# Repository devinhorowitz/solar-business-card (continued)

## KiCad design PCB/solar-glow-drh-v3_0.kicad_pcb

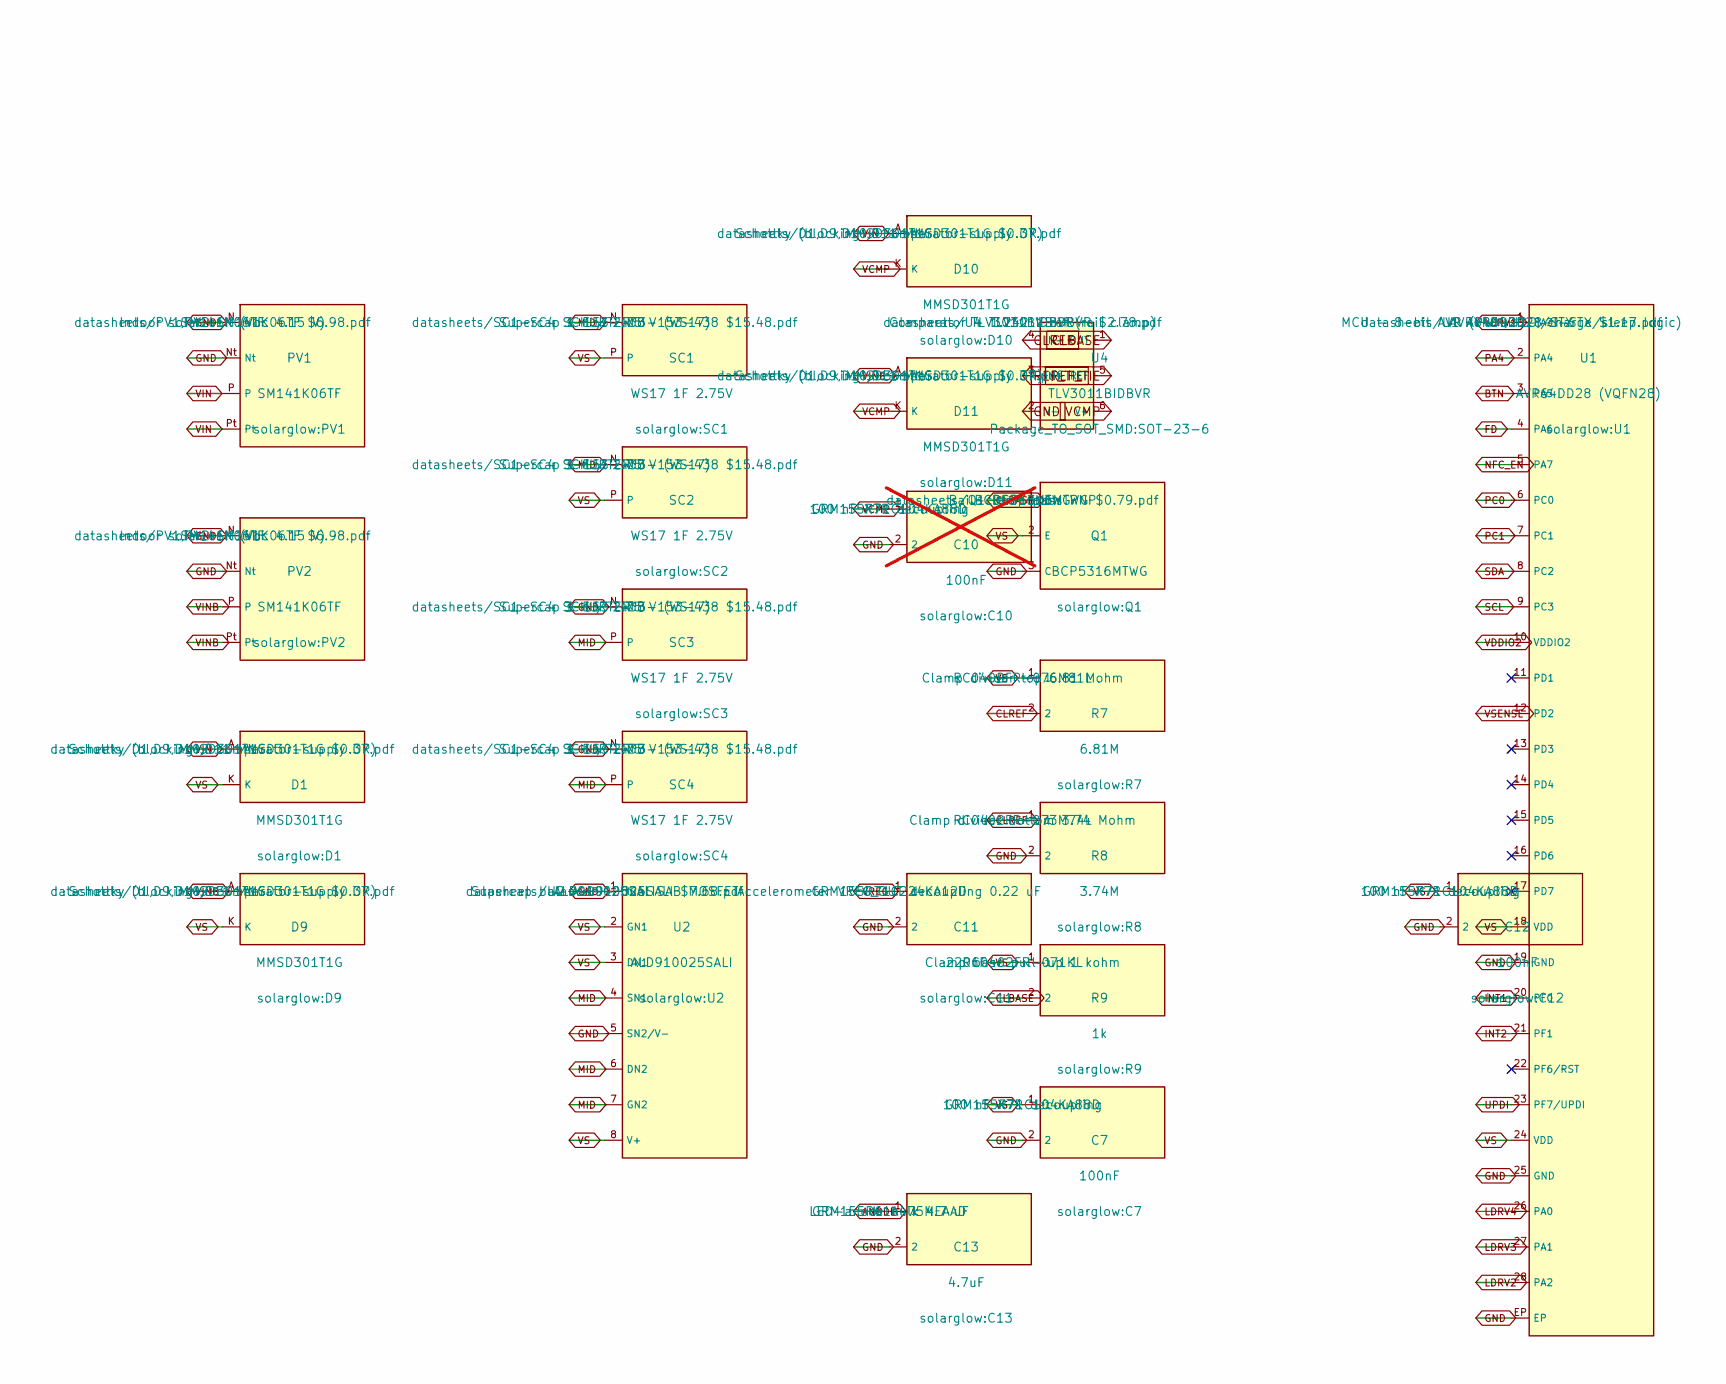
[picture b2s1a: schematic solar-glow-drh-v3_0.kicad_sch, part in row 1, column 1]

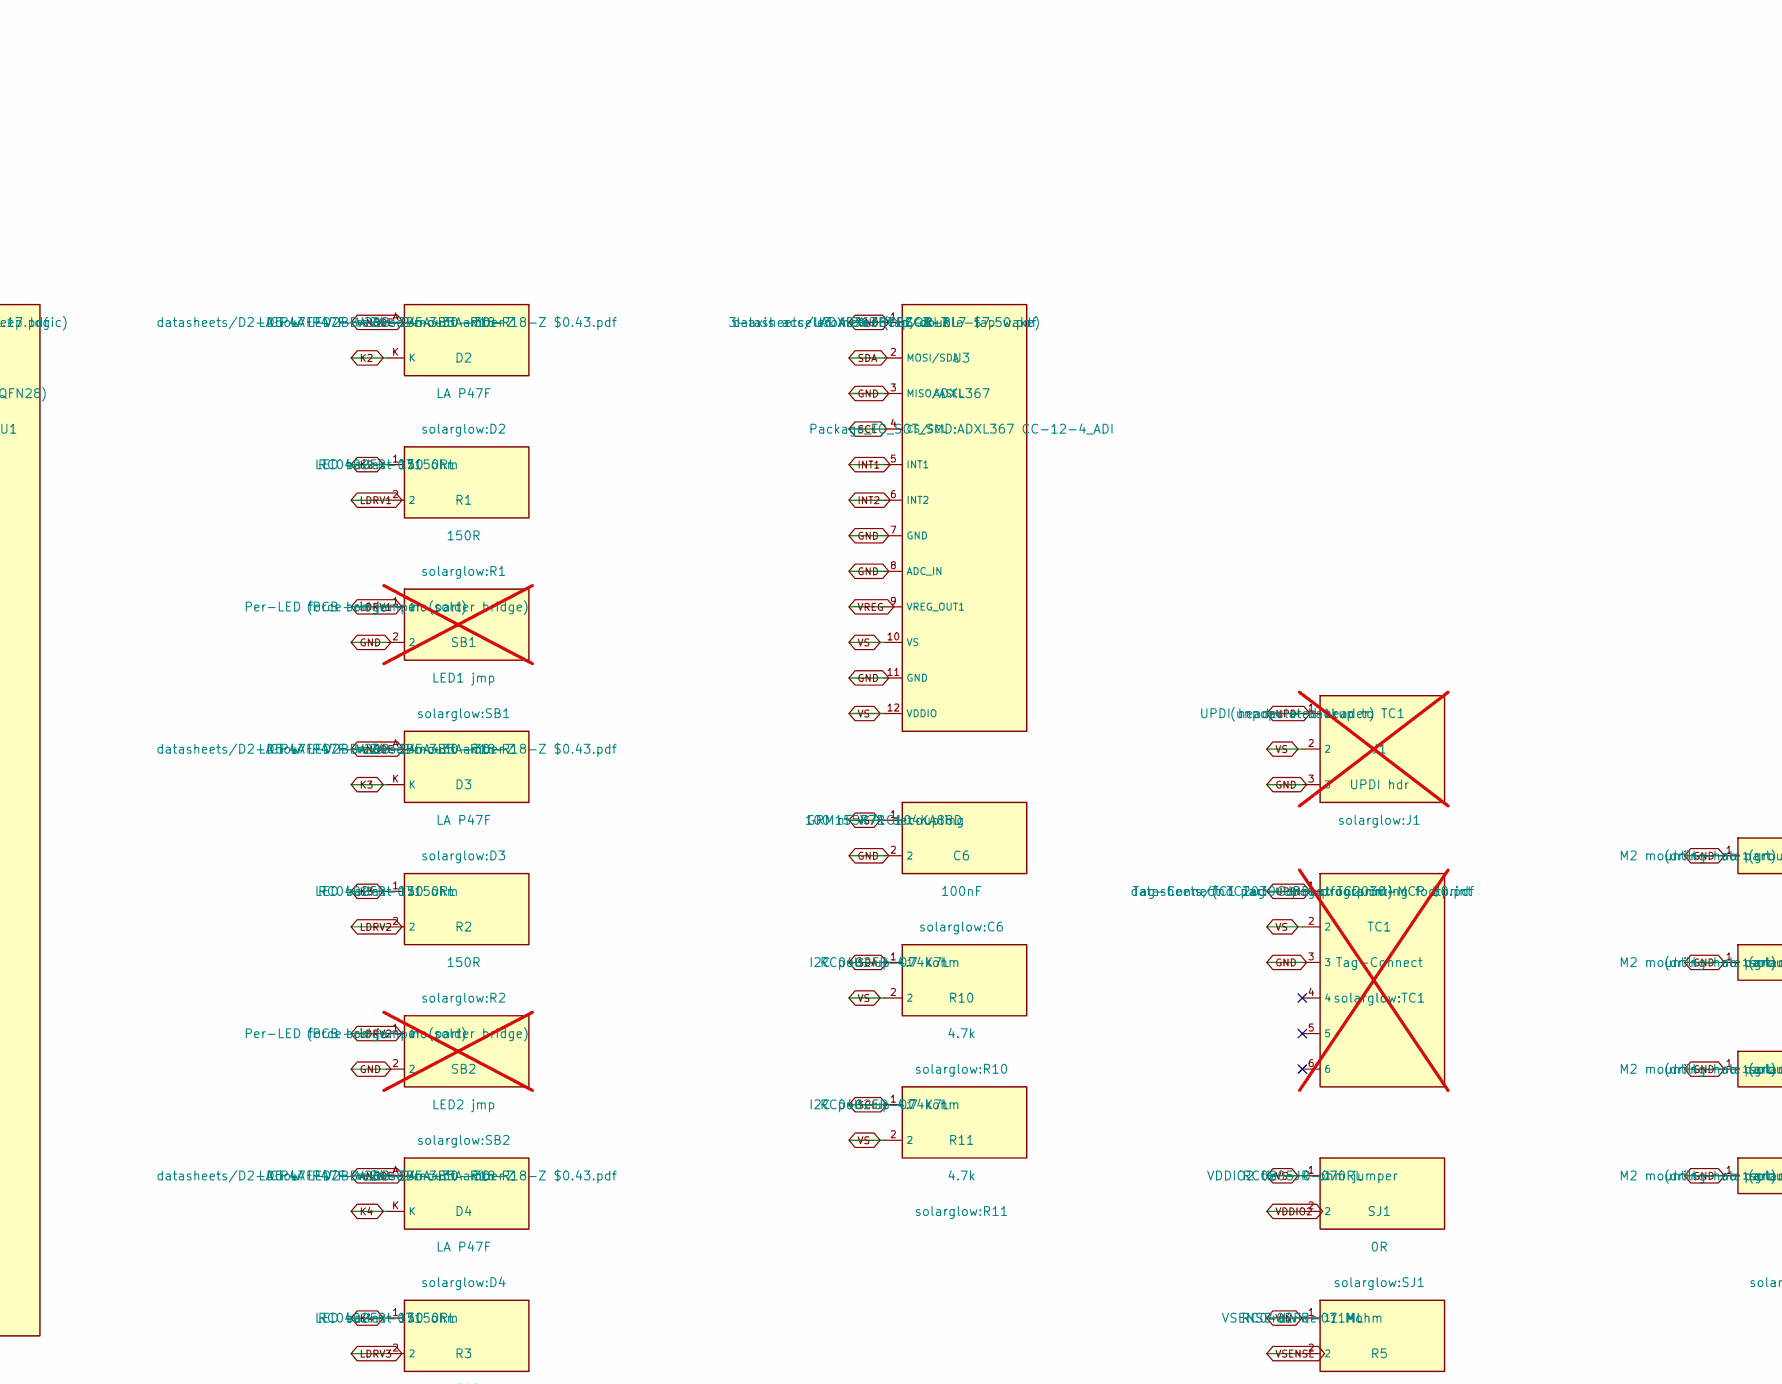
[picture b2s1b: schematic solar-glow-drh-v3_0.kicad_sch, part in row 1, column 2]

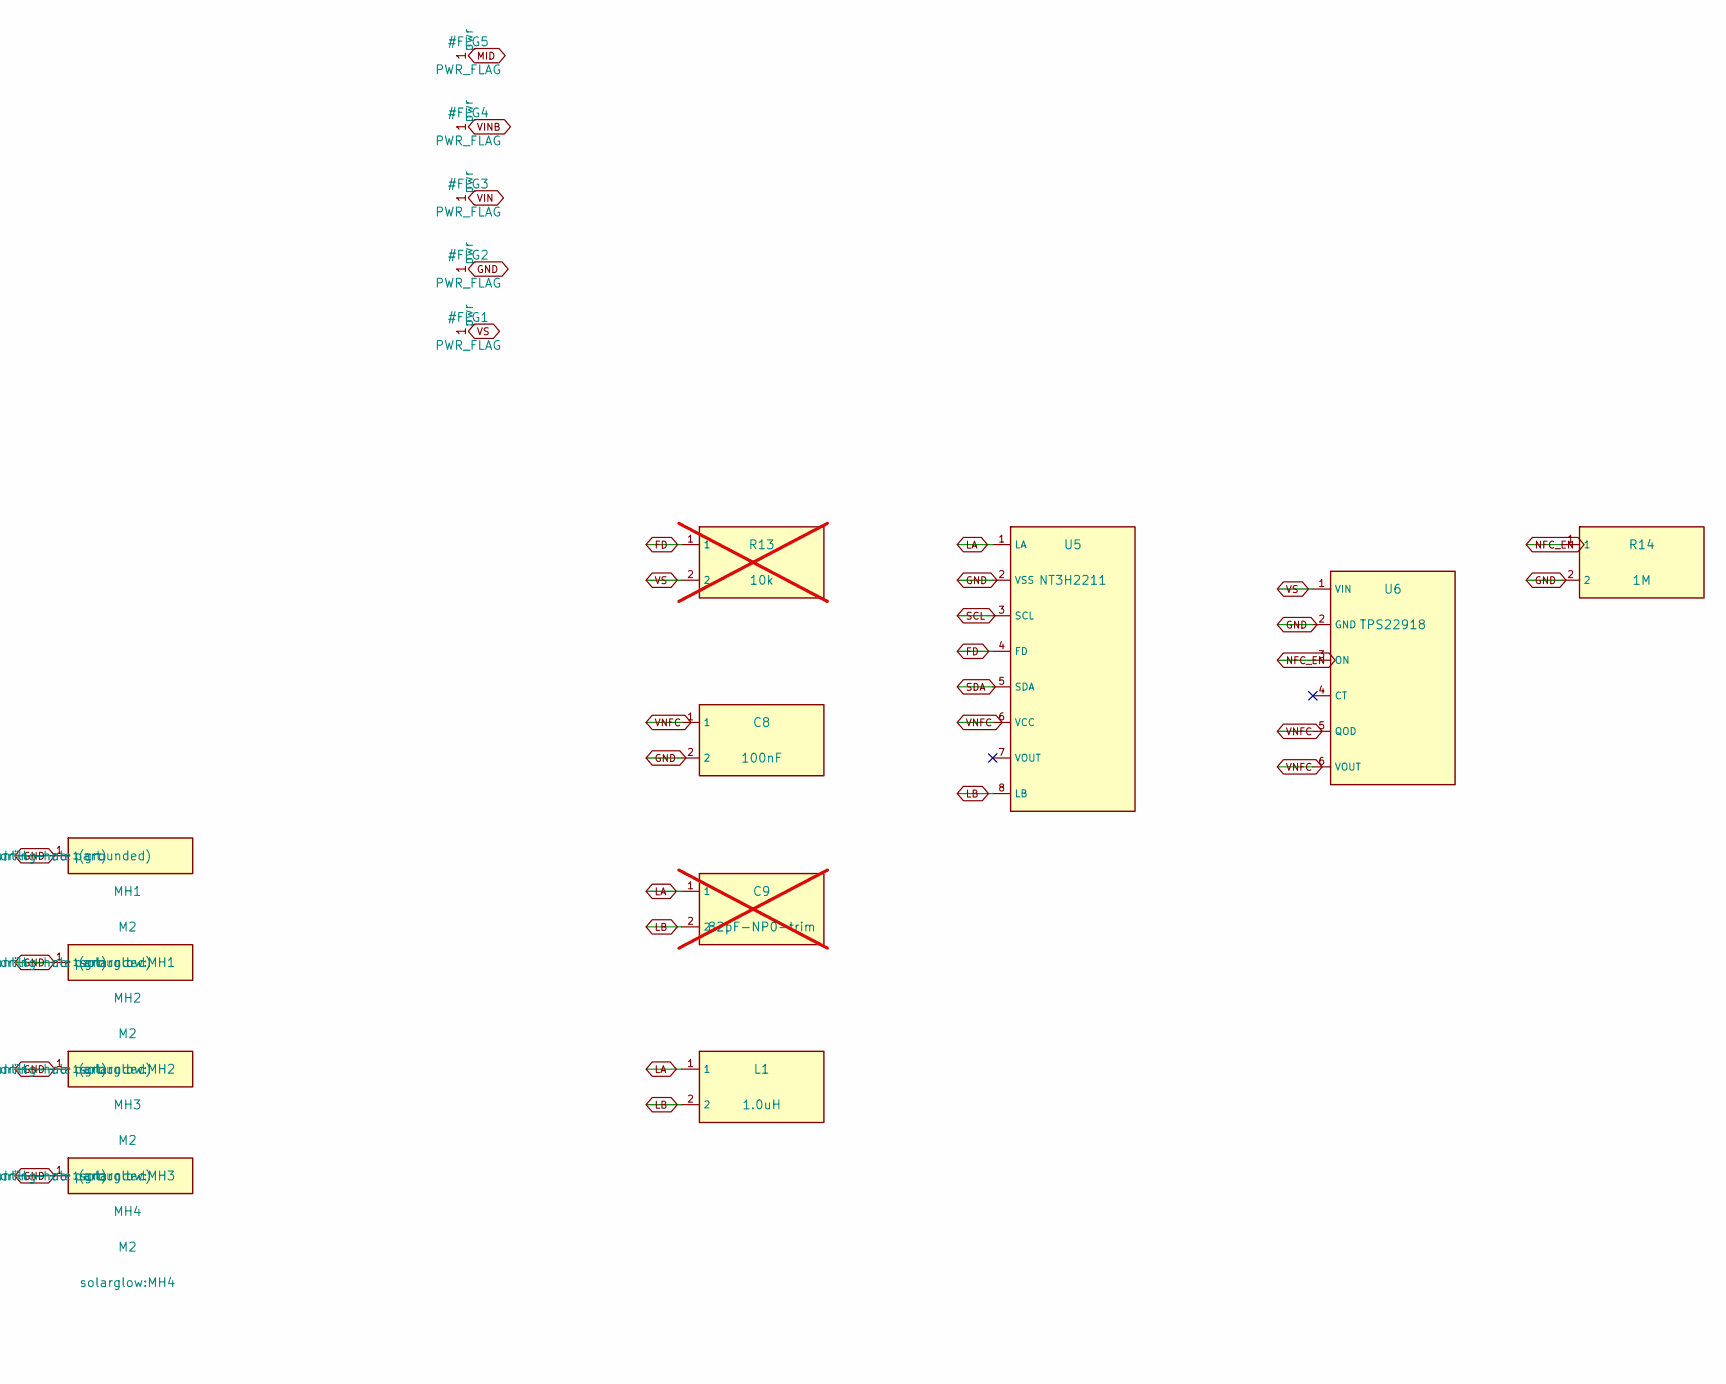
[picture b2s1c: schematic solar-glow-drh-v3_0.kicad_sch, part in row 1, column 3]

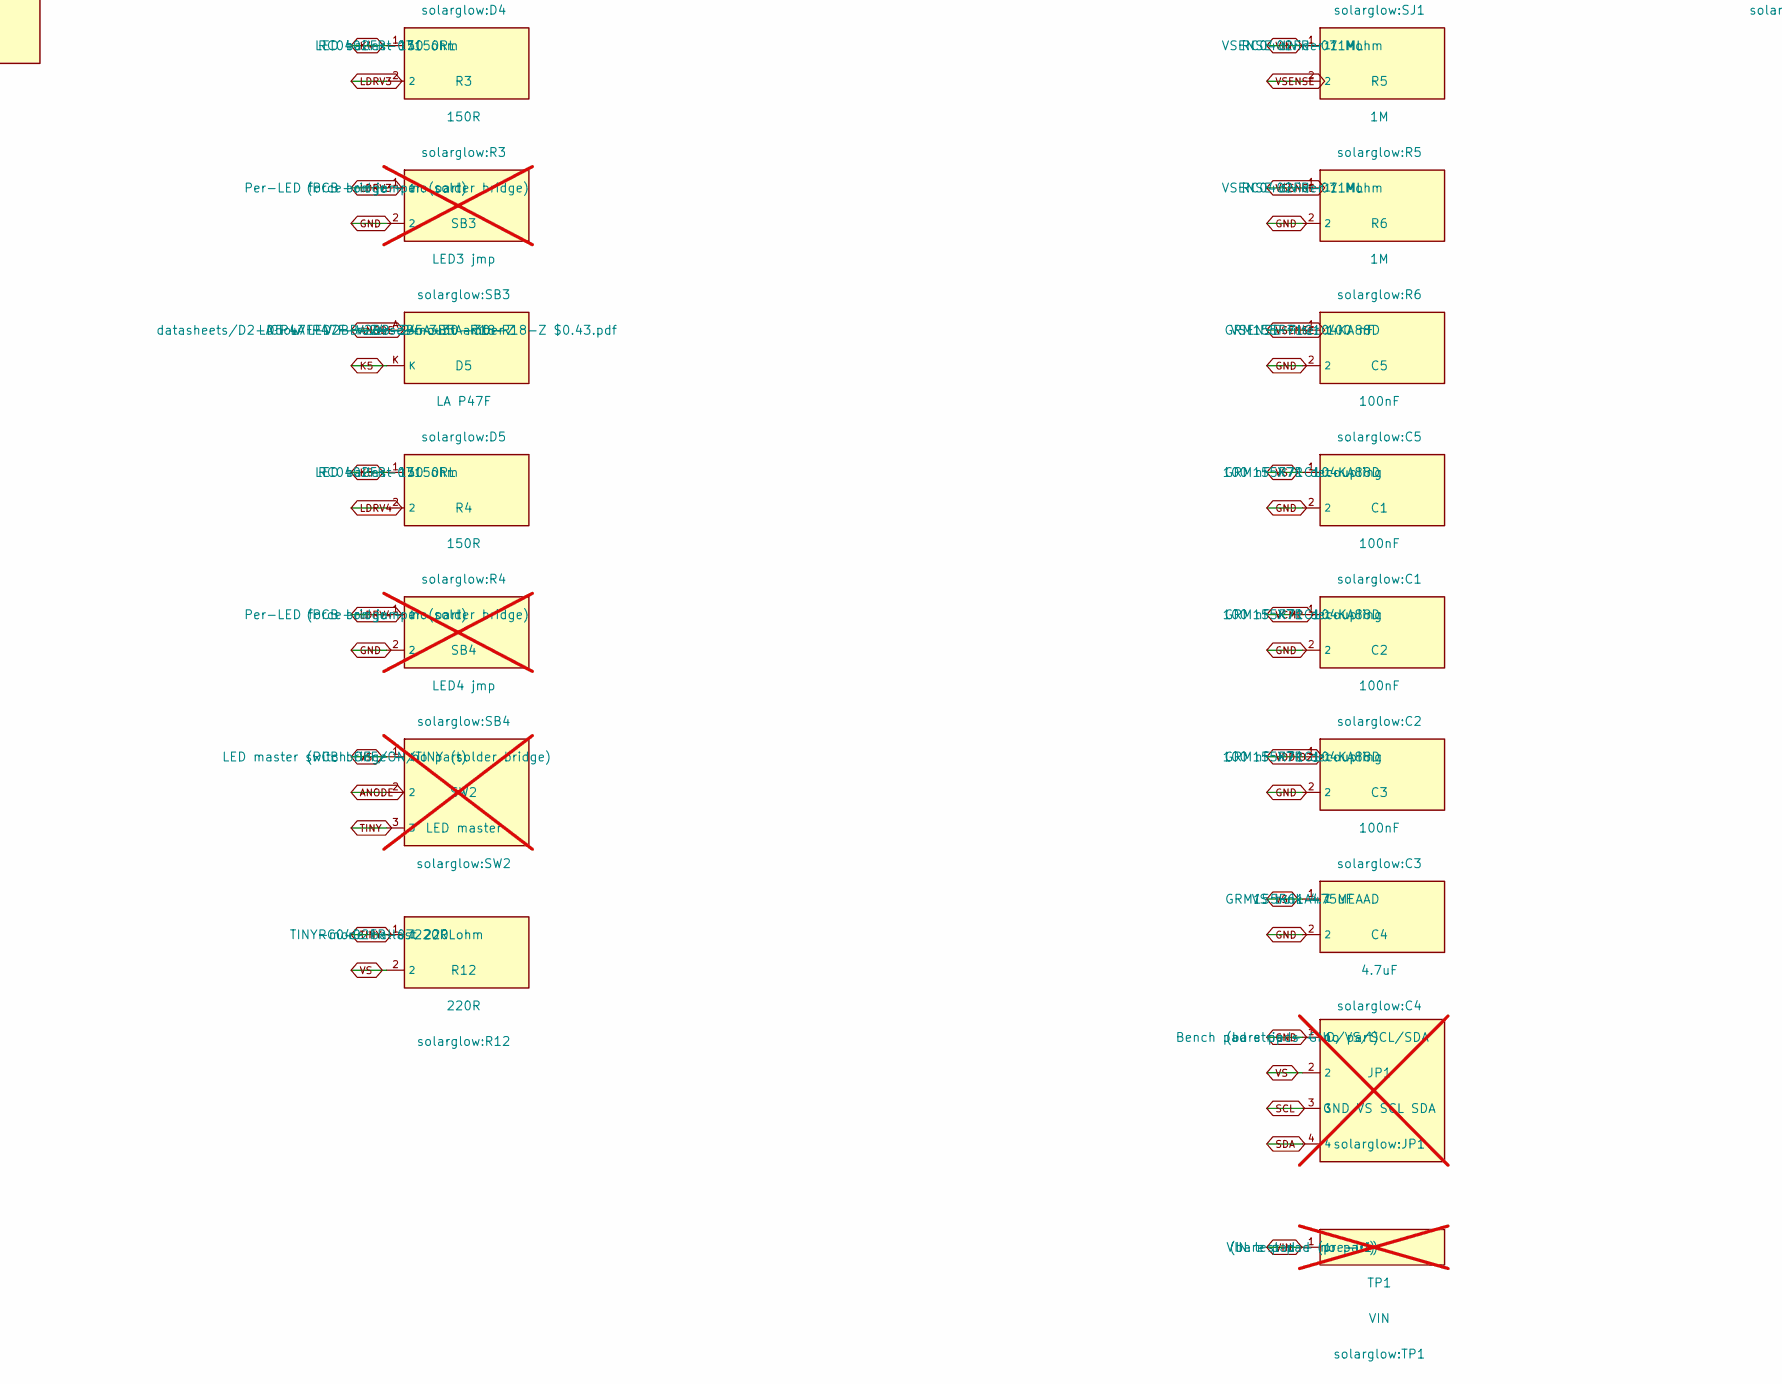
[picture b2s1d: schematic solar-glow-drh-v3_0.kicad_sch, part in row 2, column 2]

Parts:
C1: 100nF; C1; MPN GRM155R71C104KA88D
C2: 100nF; C2; MPN GRM155R71C104KA88D
C3: 100nF; C3; MPN GRM155R71C104KA88D
C4: 4.7uF; C4; MPN GRM155R61A475MEAAD
C5: 100nF; C5; MPN GRM155R71C104KA88D
C6: 100nF; C6; MPN GRM155R71C104KA88D
C7: 100nF; C7; MPN GRM155R71C104KA88D
C8: 100nF; C8; MPN GRM155R71C104KA88D
C9: 82pF-NP0-trim; C9; MPN (DNP); not fitted
C10: 100nF; C10; MPN GRM155R71C104KA88D; not fitted
C11: 220nF; C11; MPN GRM155R71C224KA12D
C12: 100nF; C12; MPN GRM155R71C104KA88D
C13: 4.7uF; C13; MPN GRM155R61A475MEAAD
D1: MMSD301T1G; D1; MPN MMSD301T1G
D2: LA P47F; D2; MPN LA P47F-V2BB-24-3B5A-30-R18-Z
D3: LA P47F; D3; MPN LA P47F-V2BB-24-3B5A-30-R18-Z
D4: LA P47F; D4; MPN LA P47F-V2BB-24-3B5A-30-R18-Z
D5: LA P47F; D5; MPN LA P47F-V2BB-24-3B5A-30-R18-Z
D9: MMSD301T1G; D9; MPN MMSD301T1G
D10: MMSD301T1G; D10; MPN MMSD301T1G
D11: MMSD301T1G; D11; MPN MMSD301T1G
J1: UPDI hdr; J1; MPN (unpopulated header); not fitted
JP1: GND VS SCL SDA; JP1; MPN (bare pads - no part); not fitted
L1: 1.0uH; MPN (PCB feature - no part)
MH1: M2; MH1; MPN (drill - no part)
MH2: M2; MH2; MPN (drill - no part)
MH3: M2; MH3; MPN (drill - no part)
MH4: M2; MH4; MPN (drill - no part)
PV1: SM141K06TF; PV1; MPN SM141K06TF
PV2: SM141K06TF; PV2; MPN SM141K06TF
Q1: BCP5316MTWG; Q1; MPN BCP5316MTWG
R1: 150R; R1; MPN RC0402FR-07150RL
R2: 150R; R2; MPN RC0402FR-07150RL
R3: 150R; R3; MPN RC0402FR-07150RL
R4: 150R; R4; MPN RC0402FR-07150RL
R5: 1M; R5; MPN RC0402FR-071ML
R6: 1M; R6; MPN RC0402FR-071ML
R7: 6.81M; R7; MPN RC0402FR-076M81L
R8: 3.74M; R8; MPN RC0402FR-073M74L
R9: 1k; R9; MPN RC0402FR-071KL
R10: 4.7k; R10; MPN RC0402FR-074K7L
R11: 4.7k; R11; MPN RC0402FR-074K7L
R12: 220R; R12; MPN RC0402FR-07220RL
R13: 10k; R13; MPN RC0402FR-0710KL; not fitted
R14: 1M; R14; MPN RC0402FR-071ML
SB1: LED1 jmp; SB1; MPN (PCB bridge - no part); not fitted
SB2: LED2 jmp; SB2; MPN (PCB bridge - no part); not fitted
SB3: LED3 jmp; SB3; MPN (PCB bridge - no part); not fitted
SB4: LED4 jmp; SB4; MPN (PCB bridge - no part); not fitted
SC1: WS17 1F 2.75V; SC1; MPN 3-153-438
SC2: WS17 1F 2.75V; SC2; MPN 3-153-438
SC3: WS17 1F 2.75V; SC3; MPN 3-153-438
SC4: WS17 1F 2.75V; SC4; MPN 3-153-438
SJ1: 0R; SJ1; MPN RC0805JR-070RL
SW2: LED master; SW2; MPN (PCB bridge - no part); not fitted
TC1: Tag-Connect; TC1; MPN (no part - pogo footprint); not fitted
TP1: VIN; TP1; MPN (bare pad - no part); not fitted
U1: AVR64DD28 (VQFN28); U1; MPN AVR64DD28-I/STX
U2: ALD910025SALI; U2; MPN ALD910025SALI
U3: ADXL367; ADXL367 CC-12-4_ADI; MPN ADXL367BCCZ-RL7
U4: TLV3011BIDBVR; SOT-23-6; MPN TLV3011BIDBVR
U5: NT3H2211; U5; MPN NT3H2211W0FHKH
U6: TPS22918; SOT-23-6; MPN TPS22918DBVR

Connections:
ANODE: C13.1, D2.A, D3.A, D4.A, D5.A, SW2.2
BTN: U1.3 (PA5)
CLBASE: Q1.1 (B), R9.2, U4.1 (OUT)
CLREF: R7.2, R8.1, U4.4 (IN-)
FD: R13.1, U1.4 (PA6), U5.4 (FD)
GND: C1.2, C2.2, C3.2, C4.2, C5.2, C6.2, C7.2, C8.2, C10.2, C11.2, C12.2, C13.2, J1.3, JP1.1 (A_A), MH1.1 (1_1), MH2.1 (1_1), MH3.1 (1_1), MH4.1 (1_1), PV1.N, PV1.Nt, PV2.N, PV2.Nt, Q1.3 (C), R6.2, R8.2, R14.2, SB1.2, SB2.2, SB3.2, SB4.2, SC3.N, SC4.N, TC1.3, U1.19 (GND), U1.25 (GND), U1.EP, U2.1 (IC), U2.5 (SN2/V-), U3.1 (SCL), U3.3 (SDO/SA0), U3.7 (GND), U3.8 (GND), U3.11 (INT2), U4.2 (V-), U5.2 (VSS), U6.2 (GND)
INT1: U1.20 (PF0), U3.5 (RES)
INT2: U1.21 (PF1), U3.6 (GND)
K2: D2.K, R1.1
K3: D3.K, R2.1
K4: D4.K, R3.1
K5: D5.K, R4.1
LA: C9.1, L1.1, U5.1 (LA)
LB: C9.2, L1.2, U5.8 (LB)
LDRV1: R1.2, SB1.1, U1.1 (PA3)
LDRV2: R2.2, SB2.1, U1.28 (PA2)
LDRV3: R3.2, SB3.1, U1.27 (PA1)
LDRV4: R4.2, SB4.1, U1.26 (PA0)
MID: SC1.N, SC2.N, SC3.P, SC4.P, U2.4 (SN1), U2.6 (DN2), U2.7 (GN2)
NFC_EN: R14.1, U1.5 (PA7), U6.3 (ON)
PA4: U1.2 (PA4)
PC0: U1.6 (PC0)
PC1: U1.7 (PC1)
REF_TIE: U4.3 (IN+), U4.5 (REF)
SCL: JP1.3 (A_A), R11.1, U1.9 (PC3), U3.4 (SDA), U5.3 (SCL)
SDA: JP1.4 (A_A), R10.1, U1.8 (PC2), U3.2 (CS), U5.5 (SDA)
TINY: R12.1, SW2.3
UPDI: J1.1, TC1.1, U1.23 (PF7/UPDI)
VCMP: C2.1, C10.1, D10.K, D11.K, U4.6 (V+)
VDDIO2: C3.1, SJ1.2, U1.10 (VDDIO2)
VIN: D1.A, D10.A, PV1.P, PV1.Pt, R5.1, TP1.1 (A_A)
VINB: D9.A, D11.A, PV2.P, PV2.Pt
VNFC: C8.1, U5.6 (VCC), U6.5 (QOD), U6.6 (VOUT)
VREG: C11.1, U3.9 (Vdd)
VS: C1.1, C4.1, C6.1, C7.1, C12.1, D1.K, D9.K, J1.2, JP1.2 (A_A), Q1.2 (E), R7.1, R9.1, R10.2, R11.2, R12.2, R13.2, SC1.P, SC2.P, SJ1.1, SW2.1, TC1.2, U1.18 (VDD), U1.24 (VDD), U2.2 (GN1), U2.3 (DN1), U2.8 (V+), U3.10 (Vdd_IO), U3.12 (INT1), U6.1 (VIN)
VSENSE: C5.1, R5.2, R6.1, U1.12 (PD2)

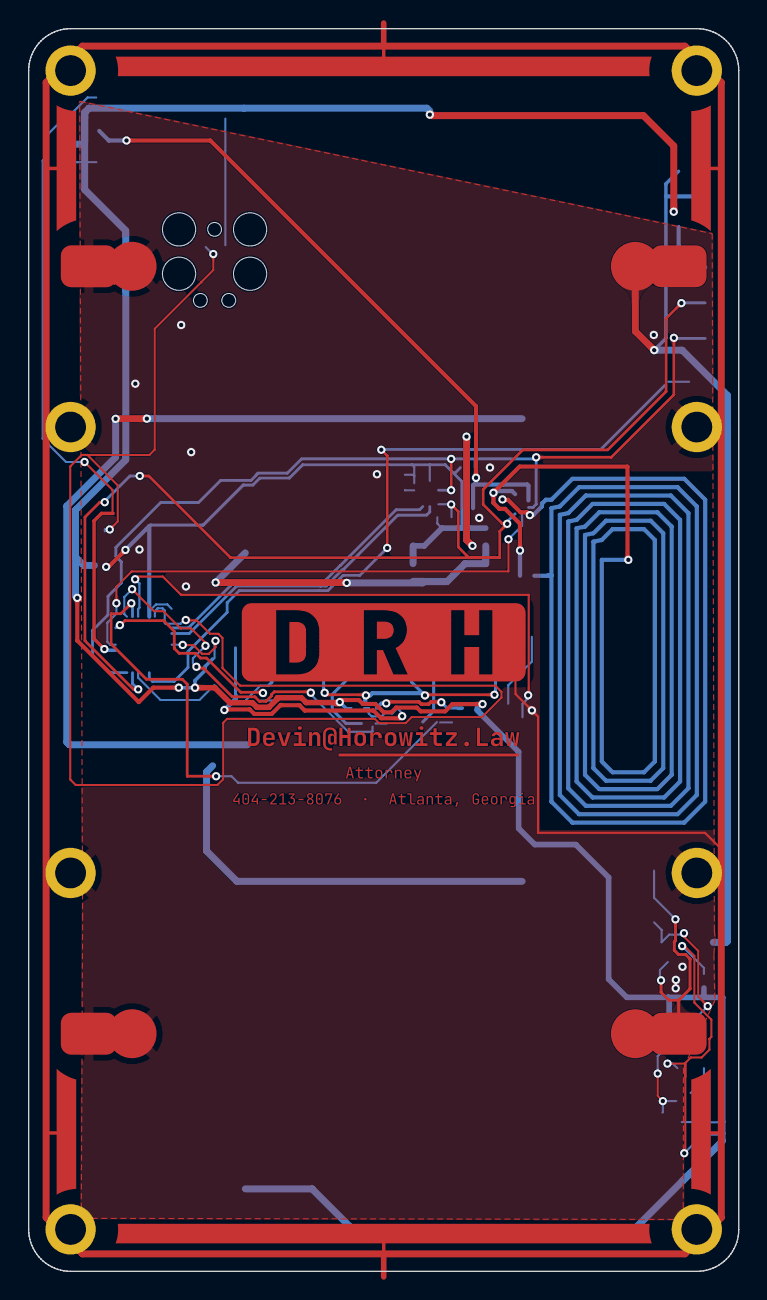
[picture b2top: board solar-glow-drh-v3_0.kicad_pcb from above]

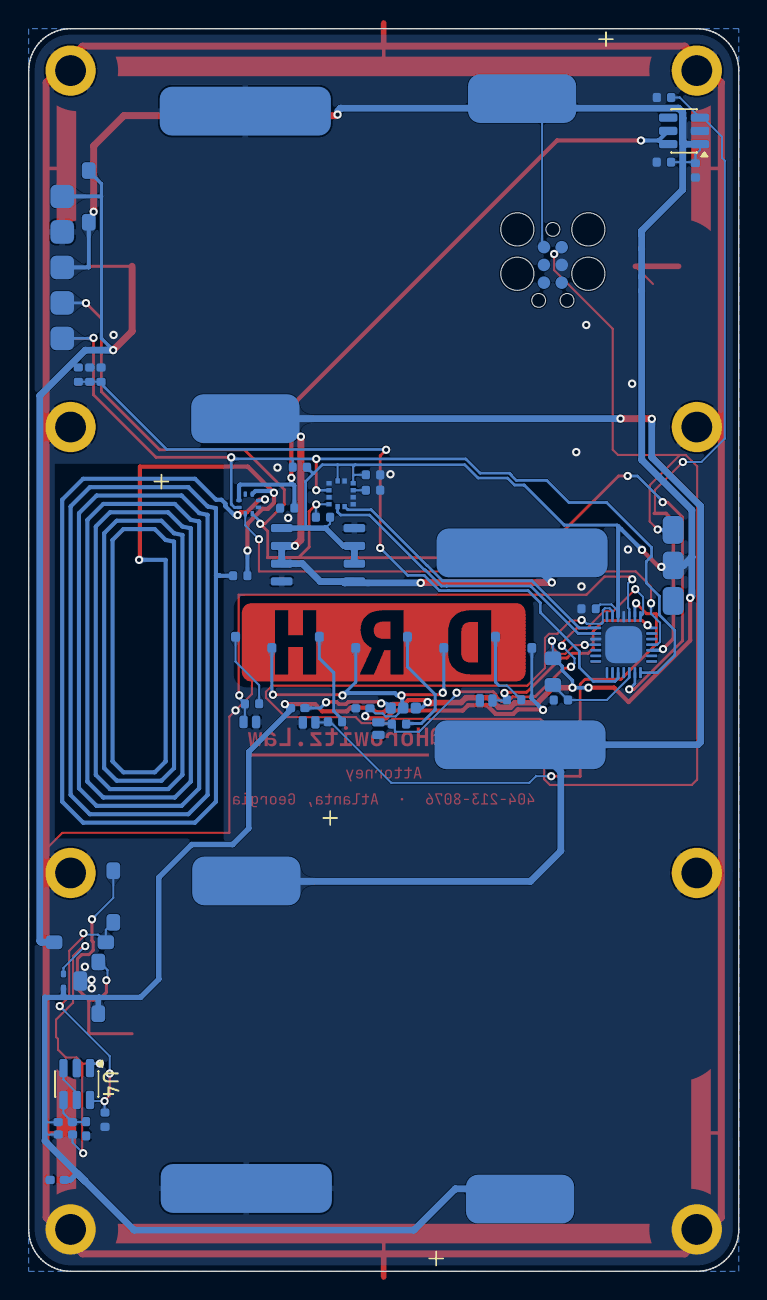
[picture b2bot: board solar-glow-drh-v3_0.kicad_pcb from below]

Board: 2 copper layers, 50.8 x 88.9 mm, 60 parts (54 on the bottom side), 32 nets.

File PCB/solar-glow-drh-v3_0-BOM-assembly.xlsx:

Ref(s) | Qty | Function | Value | Package / Footprint | Mfr | MPN (orderable) | ≈$/ea* | Ext $ | Status | Sourcing note / flag | Datasheet (repo) | DigiKey P/N
U1 | 1 | MCU — 8-bit AVR; PWM, I²C, charge/sleep logic | AVR64DD28, 64 KB, 24 MHz | VQFN-28 (4×4×1.0 mm, w/ EP) | Microchip | AVR64DD28-I/STX | 1.52 | 1.52 | LOCKED | VQFN land has an exposed pad → EP to GND. /STX confirmed = VQFN-28 (4×4). | U1 AVR64DD28-I-STX $1.17.pdf | (by MPN)
D1, D9 | 2 | Per-panel blocking Schottky (VIN/VINB→VS); isolates cells + caps in the dark | Schottky, Vf≈0.3–0.6 V | SOD-123 | onsemi | MMSD301T1G | 0.125 | 0.25 | LOCKED | Low-Vf for the ~4 V solar; one per panel so a half-shadow can't back-feed. | D1,D9,D10,D11 MMSD301T1G $0.37.pdf | MMSD301T1GOSCT-ND
U2 | 1 | Supercap balancer — dual SAB MOSFET across the MID node (auto leakage balance; 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 | Dual SAB, ~0.3 nA–1 mA | SOIC-8 | Advanced Linear Devices | ALD910025SALI | 7.68 | 7.68 | LOCKED | U2 ALD910025SALI $7.68.pdf is the combined 810025/910025 datasheet — it covers 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 | U2 ALD910025SALI $7.68.pdf | ALD910025SALI-ND
D2–D5 | 4 | Glow LEDs — reverse-mount; emit through the bare-FR4 'DRH' window | Amber 617 nm, Vf≈2.25 V | SMD, 3.4x1.9 mm | ams OSRAM | LA P47F-V2BB-24-3B5A-30-R18-Z | 0.273 | 1.092 | LOCKED | Reverse-mount; light path runs through the all-layer keepout window. | D2-D5 LA P47F-V2BB-24-3B5A-30-R18-Z $0.43.pdf | 475-LAP47F-V2BB-24-3B5A-30-R18-ZCT-ND
R1–R4 | 4 | LED ballast — one per LED; sets per-LED current (low-side PWM) | 150 Ω, ±1% | 0402 | Yageo | RC0402FR-07150RL | 0.1 | 0.4 | SIZED | Package corrected to 0402 to match the placed land (BOM previously listed 1206;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 | — | (by MPN)
R12 | 1 | TINY-mode ballast — dims all LEDs via SW2 'TINY' for long-runtime glow | 220 Ω, ±1% | 0402 | Yageo | RC0402FR-07220RL |  |  | LOCKED | Sets the SW2 TINY dim level; tunable. [v3.0: 0402 to match board land; price TB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 | — | (by MPN)
R5, R6 | 2 | VSENSE divider — taps the solar input (VIN÷2) into PD2 | 1 MΩ, ±1% | 0402 | Yageo | RC0402FR-071ML |  |  | LOCKED | R5=R6 → VSENSE = VIN/2 (tracks light, ~0 V dark). Feeds ADC + the AC0 wake-on-l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 | — | (by MPN)
C5 | 1 | VSENSE filter cap | 100 nF, X7R, 16 V | 0402 | Murata | GRM155R71C104KA88D |  |  | LOCKED | RC filter on the VSENSE node. [v3.0: 0402 to match board land; price TBC] | (Murata GRM155 family) | (by MPN)
U3 | 1 | 3-axis accelerometer — tap/double-tap wake; INT1/INT2 → PF1/PF0 | I²C 0x1D, ±2–8 g | LGA-12 CC-12-4 (2.2×2.3×0.87 mm) | Analog Devices | ADXL367BCCZ-RL7 | 7.5 | 7.5 | LOCKED | SCLK→GND (I²C); ASEL (pin 3)→GND ⇒ addr 0x1D. FOOTPRINT = placeholder ST land r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 | datasheets/U3 ADXL367BCCZ-RL7 $7.50.pdf | (by MPN)
R10, R11 | 2 | I²C pull-ups (TWI0 host on PC2/PC3) → VS | 4.7 kΩ, ±1% | 0402 | Yageo | RC0402FR-074K7L |  |  | LOCKED | Required — open-drain TWI bus. Firmware must set TWIROUTEA = ALT2. [v3.0: 0402 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 | — | (by MPN)
U4 | 1 | Comparator + 1.242 V ref, open-drain | TLV3011BIDBVR | SOT-23-6 | Texas Instruments | TLV3011BIDBVR | 2.78 | 2.78 | LOCKED | TLV3011B comparator (SOT-23-6). Corrected 2026-07-04 from the stale v2 TLV431B 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 | U4 TLV3011BIDBVR $2.78.pdf | (by MPN)
Q1 | 1 | Rail-clamp pass PNP — shunts VS→GND when U4 trips | PNP (BCP53 family) | SOT / WDFN | onsemi | BCP5316MTWG | 0.45 | 0.45 | LOCKED | Emitter=VS, collector=GND, base=CLBASE. | Q1 BCP5316MTWG $0.79.pdf | (by MPN)
R7 | 1 | Clamp divider top — sets VS trip with R8 | 1.8 MΩ, ±1% | 0402 | Yageo | RC0402FR-071M8L |  |  | LOCKED | Trip = 1.24×(1+R7/R8) = 3.47 V. [v3.0: 0402 to match board land; price TBC] | — | (by MPN)
R8 | 1 | Clamp divider bottom | 1 MΩ, ±1% | 0402 | Yageo | RC0402FR-071ML |  |  | LOCKED | Divider midpoint (CLREF) → TLV431 ref. [v3.0: 0402 to match board land; price T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 | — | (by MPN)
R9 | 1 | Clamp base pull-up / cathode path | 1 kΩ, ±1% | 0402 | Yageo | RC0402FR-071KL |  |  | LOCKED | VS→CLBASE; holds Q1 off until U4 conducts. [v3.0: 0402 to match board land; pri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 | — | (by MPN)
C1 | 1 | MCU decoupling (VDD) | 100 nF, X7R, 16 V | 0402 | Murata | GRM155R71C104KA88D |  |  | LOCKED | [v3.0: 0402 to match board land; price TBC] | (Murata GRM155 family) | (by MPN)
C2, C3 | 2 | Decoupling — VDDIO2 / MCU | 100 nF, X7R, 16 V | 0402 | Murata | GRM155R71C104KA88D |  |  | LOCKED | [v3.0: 0402 to match board land; price TBC] | (Murata GRM155 family) | (by MPN)
C4 | 1 | VS-rail bulk decoupling | 4.7 µF, X5R, 10 V | 0402 | Murata | GRM155R61A475MEAAD |  |  | LOCKED | [v3.0: 0402 to match board land; price TBC] | (Murata GRM155 family) | (by MPN)
C6 | 1 | Accelerometer decoupling | 100 nF, X7R, 16 V | 0402 | Murata | GRM155R71C104KA88D |  |  | LOCKED | [v3.0: 0402 to match board land; price TBC] | (Murata GRM155 family) | (by MPN)
C11 | 1 | Accelerometer VREG_OUT decoupling (mandatory) | 0.2 µF, X7R, 16 V | 0402 | Murata | GRM155R71C224KA12D |  |  | LOCKED | ADXL367 pin 9 VREG_OUT1 → GND. Datasheet-mandated 0.2 µF; 0.22 µF nearest std. | (Murata GRM155 family) | (by MPN)
C12 | 1 | Accelerometer VDDIO decoupling | 100 nF, X7R, 16 V | 0402 | Murata | GRM155R71C104KA88D |  |  | LOCKED | ADXL367 pin 12 VDDIO → GND. | (Murata GRM155 family) | (by MPN)
C7 | 1 | Clamp local decoupling | 100 nF, X7R, 16 V | 0402 | Murata | GRM155R71C104KA88D |  |  | LOCKED | [v3.0: 0402 to match board land; price TBC] | (Murata GRM155 family) | (by MPN)
SJ1 | 1 | VDDIO2 tie — bonds VDDIO2 to VS (MVIO unused) | 0 Ω jumper | 0805 | Yageo | RC0805JR-070RL | 0.05 | 0.05 | LOCKED |  | — | (by MPN)
U5 | 1 | NFC tag — NTAG I²C plus 2K; phone reads/writes EEPROM, FD signals field to MCU | NTAG I²C plus, 2 KB, I²C 0x55 | XQFN8 (SOT902-3, 1.6×1.6×0.5 mm) | NXP | NT3H2211W0FHKH | 0.75 | 0.75 | LOCKED | v2.2 NFC addition. XQFN8 = SOT902-3 (datasheet Table 1). I²C 0x55 (no clash w/ 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 | U5 NT3H2211W0FHKH $1.38.pdf | (by MPN)
C8 | 1 | NFC tag (U5) VCC decoupling | 100 nF, X7R, 16 V | 0402 | Murata | GRM155R71C104KA88D |  |  | LOCKED | v2.2 NFC addition. Same part as C1/C2/C3/C6/C7. [v3.0: 0402 to match board land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 | (Murata GRM155 family) | (by MPN)
C13 | 1 | LED-anode bulk — supplies the glow-PWM transient locally, keeps it off the shar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 | 4.7 µF, X5R, 10 V | 0402 | Murata | GRM155R61A475MEAAD |  |  | ADD | NEW bulk at the LED anode (LED side of SW2). ~3 uF effective at ~3.4 V after DC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 |  | (format-derived — confirm)
R13 | 1 | NFC FD pull-up — open-drain FD (U5 pin 4) → PA6 | 10 kΩ, ±1% | 0402 | Yageo | RC0402FR-0710KL |  |  | DNP | v2.2 NFC addition. Pulls open-drain FD up to VS. [v3.0: 0402 to match board lan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 | — | (by MPN)
U6 | 1 | NFC VNFC load switch — power-gates U5 VCC from PA7 (NFC_EN) | High-side load switch | SOT-23-6 (DBV) | Texas Instruments | TPS22918DBVR | 0.55 | 0.55 | LOCKED | v3.0 addition. VIN=VS, VOUT=VNFC, ON=NFC_EN, QOD strapped to VOUT (internal RPD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 | datasheets/U6 TPS22918DBVR $0.55.pdf | (by MPN)
R14 | 1 | NFC_EN pulldown — holds U6 OFF while PA7 tristates (UPDI / reset / brown-out) | 1 MΩ, ±1% | 0402 | Yageo | RC0402FR-071ML |  |  | LOCKED | v3.0 addition, placed with the R14 board patch at (4.39, 29.4). Price TBC. | — | (by MPN)
Placed-parts subtotal (per board)
NOTE: PCBWay turnkey BOM — machine-placed, bottom side, 39 parts. Converted 040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
Hand-soldered by customer, NOT on this BOM: SC1-SC4 (supercaps), PV1-PV2 (solar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
Not placed: SW2, SB1-SB4 (bridges), TC1 (Tag-Connect), J1/JP1/JP2 (headers), MH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
